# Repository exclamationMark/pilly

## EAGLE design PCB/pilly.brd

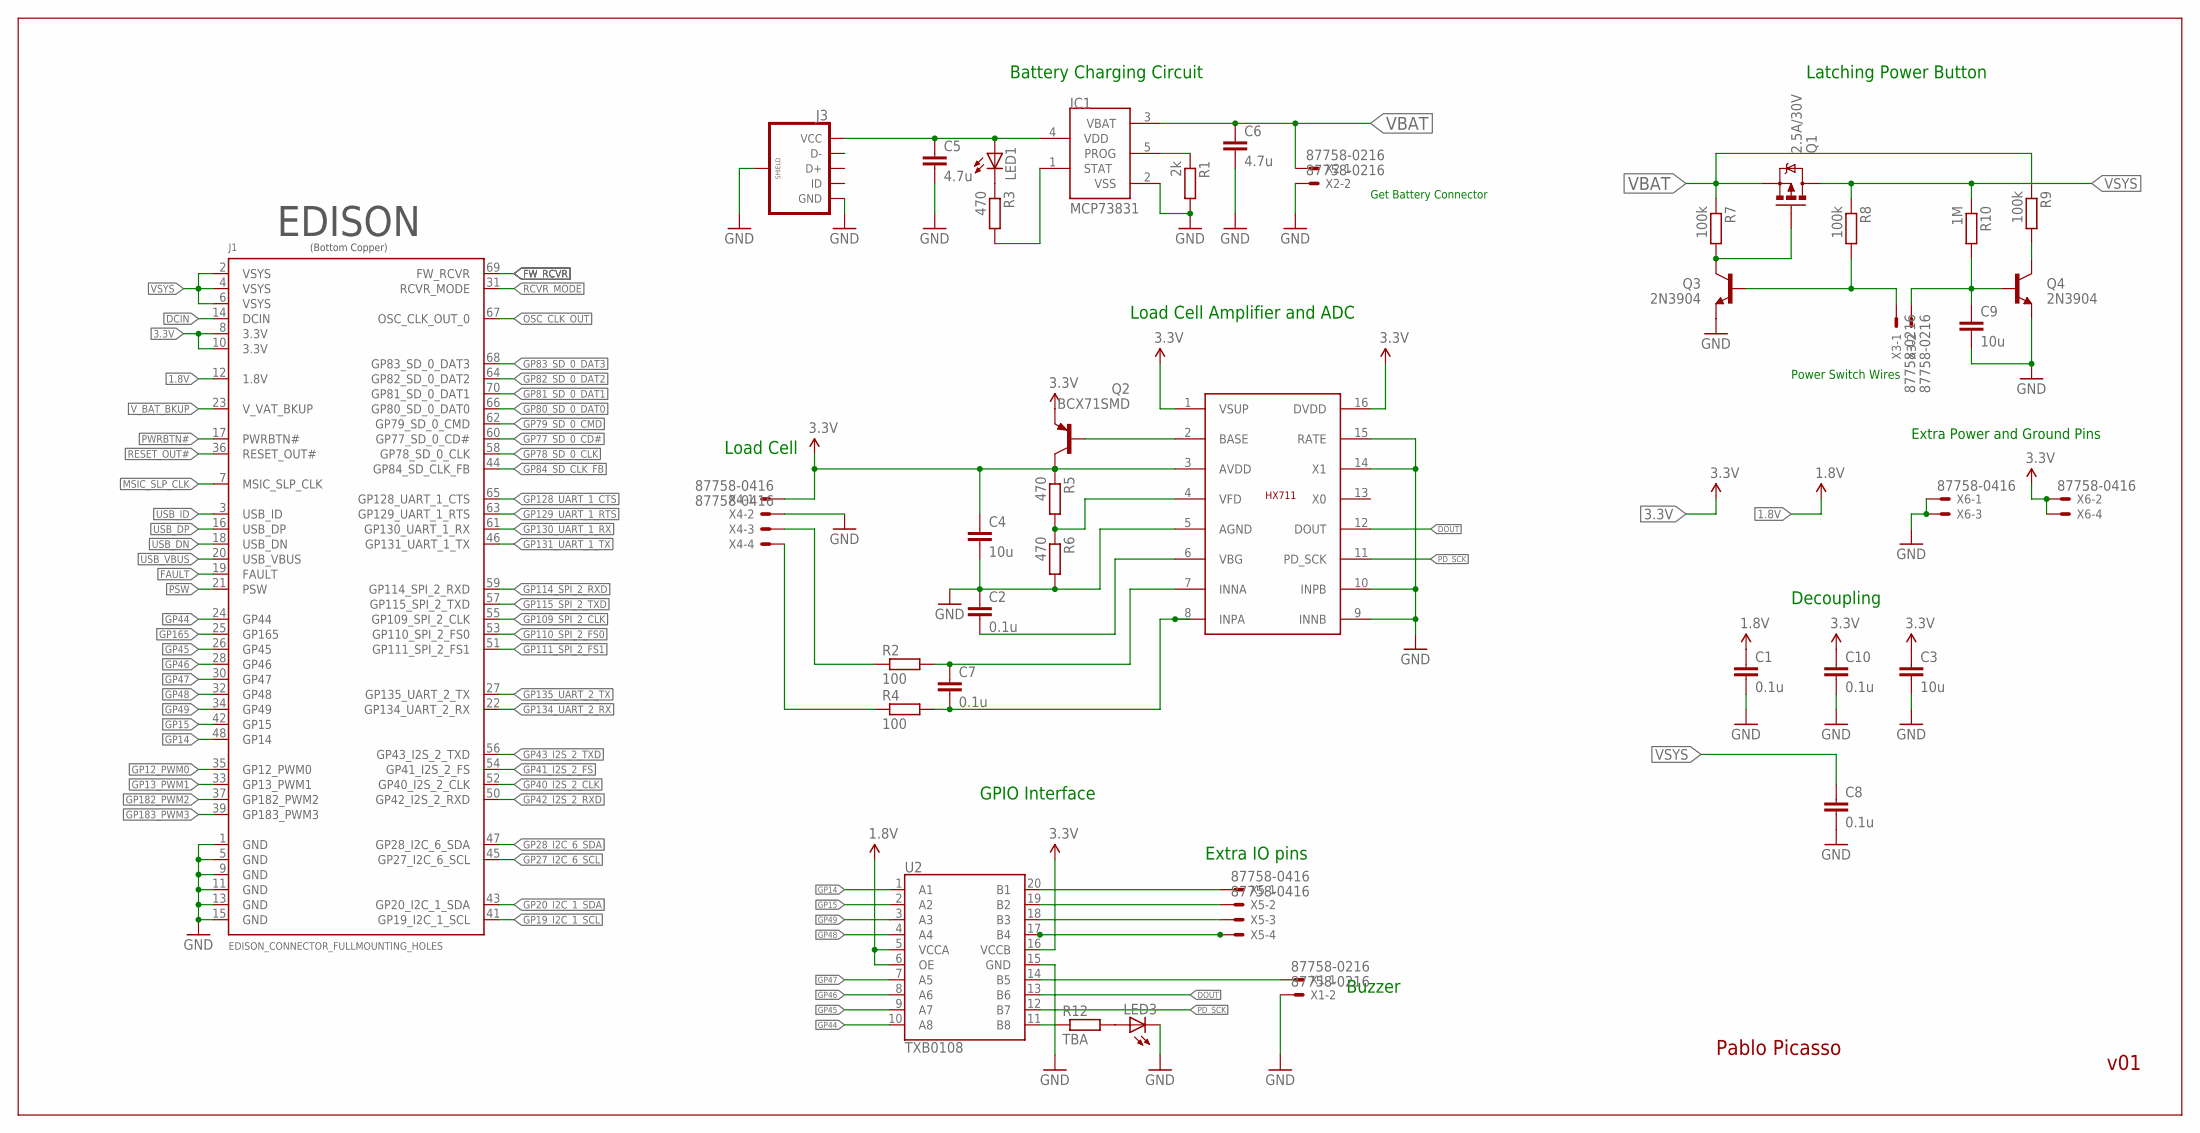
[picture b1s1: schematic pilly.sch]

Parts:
C1, C2, C7, C8, C10: 0.1u; C0805K
C3, C4, C9: 10u; C0805K
C5, C6: 4.7u; C0805K
IC1: MCP73831; SOT23-5L
J1: EDISON_CONNECTOR_FULLMOUNTING_HOLES; EDISON_DAUGHTER
J3: USB_MICROB_PLUGCONN-11752; USB-B-MICRO-SMD_V03
LED1, LED3: LEDCHIPLED_0805; CHIPLED_0805
Q1: 2.5A/30V; SOT23-3
Q2: BCX71SMD; SOT23
Q3, Q4: 2N3904; SOT23-3
R1: 2k; R0603
R2, R4: 100; R0603
R3, R5, R6: 470; R0603
R7, R8, R9: 100k; R0603
R10: 1M; R0603
R12: TBA; R0603
U2: TXB0108; UFDFN-20
U$1: HX711; SO16
X1, X2, X3: 87758-0216
X4, X5, X6: 87758-0416

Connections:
1.8V: C1.1, J1.12 (1.8V), U2.5 (VCCA), U2.6 (OE)
3.3V: C3.1, C4.1, C10.1, J1.8 (3.3V), J1.10 (3.3V), Q2.2 (E), Q2.3 (C), R5.1, U2.16 (VCCB), U$1.1 (VSUP), U$1.3 (AVDD), U$1.16 (DVDD), X4.1, X6.2, X6.4
DCIN: J1.14 (DCIN)
DOUT: U2.13 (B6), U$1.12 (DOUT)
FAULT: J1.19 (FAULT)
FW_RCVR: J1.69 (FW_RCVR)
GND: C1.2, C2.1, C3.2, C4.2, C5.2, C6.2, C8.2, C9.2, C10.2, IC1.2 (VSS), J1.1 (GND), J1.5 (GND), J1.9 (GND), J1.11 (GND), J1.13 (GND), J1.15 (GND), J3.GND, J3.SHIELD1 (SHIELD), J3.SHIELD2 (SHIELD), J3.SHIELD3 (SHIELD), LED3.C, Q3.2 (E), Q4.2 (E), R1.2, R6.2, U2.15 (GND), U$1.5 (AGND), U$1.9 (INNB), U$1.10 (INPB), U$1.14 (X1), U$1.15 (RATE), X1.2, X2.2, X4.2, X6.1, X6.3
GP12_PWM0: J1.35 (GP12_PWM0)
GP13_PWM1: J1.33 (GP13_PWM1)
GP14: J1.48 (GP14), U2.1 (A1)
GP15: J1.42 (GP15), U2.2 (A2)
GP19_I2C_1_SCL: J1.41 (GP19_I2C_1_SCL)
GP20_I2C_1_SDA: J1.43 (GP20_I2C_1_SDA)
GP27_I2C_6_SCL: J1.45 (GP27_I2C_6_SCL)
GP28_I2C_6_SDA: J1.47 (GP28_I2C_6_SDA)
GP40_I2S_2_CLK: J1.52 (GP40_I2S_2_CLK)
GP41_I2S_2_FS: J1.54 (GP41_I2S_2_FS)
GP42_I2S_2_RXD: J1.50 (GP42_I2S_2_RXD)
GP43_I2S_2_TXD: J1.56 (GP43_I2S_2_TXD)
GP44: J1.24 (GP44), U2.10 (A8)
GP45: J1.26 (GP45), U2.9 (A7)
GP46: J1.28 (GP46), U2.8 (A6)
GP47: J1.30 (GP47), U2.7 (A5)
GP48: J1.32 (GP48), U2.4 (A4)
GP49: J1.34 (GP49), U2.3 (A3)
GP77_SD_0_CD#: J1.60 (GP77_SD_0_CD#)
GP78_SD_0_CLK: J1.58 (GP78_SD_0_CLK)
GP79_SD_0_CMD: J1.62 (GP79_SD_0_CMD)
GP80_SD_0_DAT0: J1.66 (GP80_SD_0_DAT0)
GP81_SD_0_DAT1: J1.70 (GP81_SD_0_DAT1)
GP82_SD_0_DAT2: J1.64 (GP82_SD_0_DAT2)
GP83_SD_0_DAT3: J1.68 (GP83_SD_0_DAT3)
GP84_SD_CLK_FB: J1.44 (GP84_SD_CLK_FB)
GP109_SPI_2_CLK: J1.55 (GP109_SPI_2_CLK)
GP110_SPI_2_FS0: J1.53 (GP110_SPI_2_FS0)
GP111_SPI_2_FS1: J1.51 (GP111_SPI_2_FS1)
GP114_SPI_2_RXD: J1.59 (GP114_SPI_2_RXD)
GP115_SPI_2_TXD: J1.57 (GP115_SPI_2_TXD)
GP128_UART_1_CTS: J1.65 (GP128_UART_1_CTS)
GP129_UART_1_RTS: J1.63 (GP129_UART_1_RTS)
GP130_UART_1_RX: J1.61 (GP130_UART_1_RX)
GP131_UART_1_TX: J1.46 (GP131_UART_1_TX)
GP134_UART_2_RX: J1.22 (GP134_UART_2_RX)
GP135_UART_2_TX: J1.27 (GP135_UART_2_TX)
GP165: J1.25 (GP165)
GP182_PWM2: J1.37 (GP182_PWM2)
GP183_PWM3: J1.39 (GP183_PWM3)
MSIC_SLP_CLK: J1.7 (MSIC_SLP_CLK)
unnamed: LED1.C, R3.1
unnamed: IC1.5 (PROG), R1.1
unnamed: U2.14 (B5), X1.1
unnamed: R5.2, R6.1, U$1.4 (VFD)
unnamed: IC1.1 (STAT), R3.2
unnamed: C7.1, R2.2, U$1.7 (INNA)
unnamed: C7.2, R4.2, U$1.8 (INPA)
unnamed: C2.2, U$1.6 (VBG)
unnamed: Q2.1 (B), U$1.2 (BASE)
unnamed: R2.1, X4.3
unnamed: R4.1, X4.4
unnamed: U2.20 (B1), X5.1
unnamed: Q1.1 (G), Q3.3 (C), R7.2
unnamed: Q4.3 (C), R9.2
unnamed: C9.1, Q4.1 (B), R10.2, X3.2
unnamed: U2.19 (B2), X5.2
unnamed: U2.18 (B3), X5.3
unnamed: Q3.1 (B), R8.2, X3.1
unnamed: LED3.A, R12.2
unnamed: U2.17 (B4), X5.4
unnamed: R12.1, U2.11 (B8)
OSC_CLK_OUT: J1.67 (OSC_CLK_OUT_0)
PD_SCK: U2.12 (B7), U$1.11 (PD_SCK)
PSW: J1.21 (PSW)
PWRBTN#: J1.17 (PWRBTN#)
RCVR_MODE: J1.31 (RCVR_MODE)
RESET_OUT#: J1.36 (RESET_OUT#)
USB_DN: J1.18 (USB_DN)
USB_DP: J1.16 (USB_DP)
USB_ID: J1.3 (USB_ID)
USB_VBUS: J1.20 (USB_VBUS)
VBAT: C6.1, IC1.3 (VBAT), Q1.2 (S), R7.1, R9.1, X2.1
VIN: C5.1, IC1.4 (VDD), J3.VBUS (VCC), LED1.A
VSYS: C8.1, J1.2 (VSYS), J1.4 (VSYS), J1.6 (VSYS), Q1.3 (D), R8.1, R10.1
V_BAT_BKUP: J1.23 (V_VAT_BKUP)

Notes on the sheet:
v01
Battery Charging Circuit
Load Cell Amplifier and ADC
Extra IO pins
Latching Power Button
Power Switch Wires
Load Cell
Buzzer
Get Battery Connector
Decoupling
GPIO Interface
EDISON
(Bottom Copper)
Pablo Picasso
Extra Power and Ground Pins

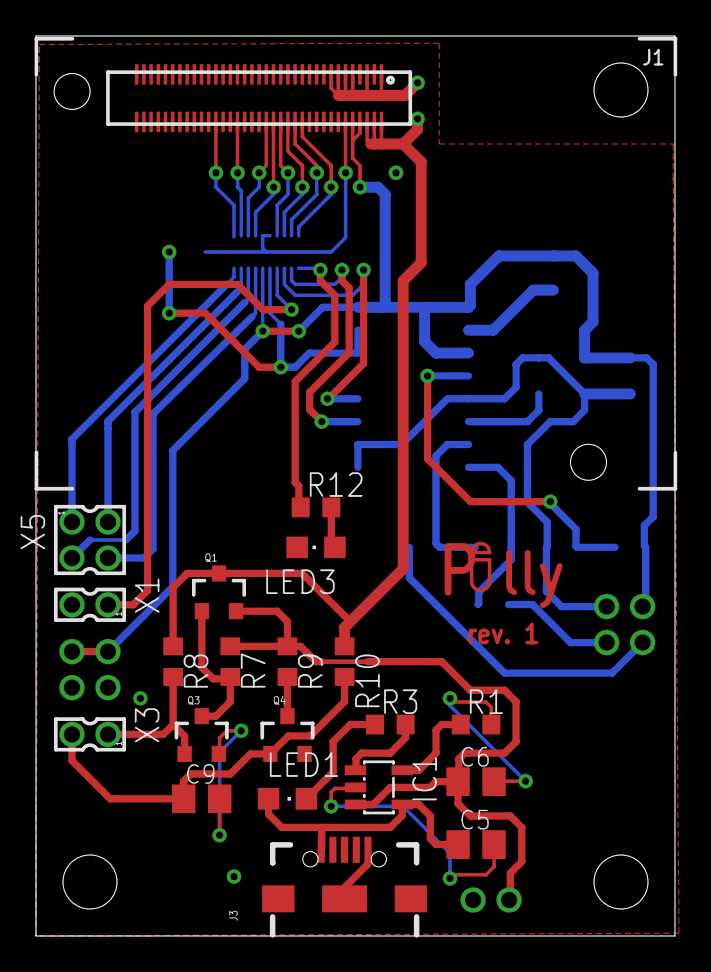
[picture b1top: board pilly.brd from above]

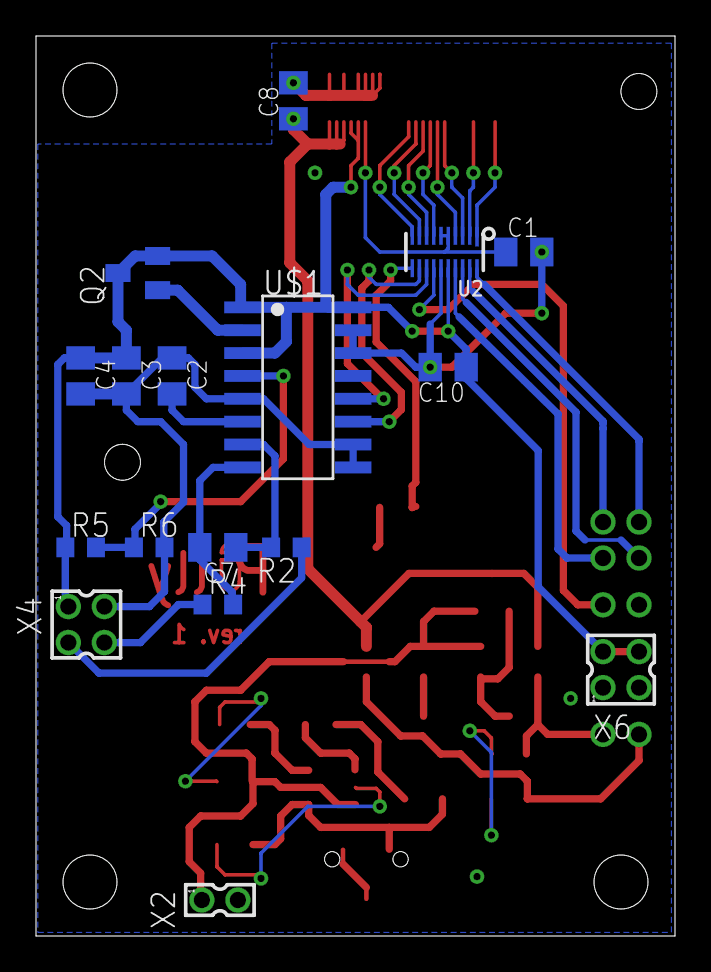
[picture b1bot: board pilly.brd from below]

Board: 2 copper layers, 35.5 x 50.0 mm, 38 parts (17 on the bottom side), 37 nets.

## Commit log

2016-03-23 initial comit, woo!
2016-03-23 web stuff
2016-03-23 Removed control_panel backup
2016-03-23 Merged style.css and control.css into one file (style.css). Started styling login page. Added test.py for local testing.
2016-03-23 MOAR login styling
2016-03-23 Root of websites now renders 'index.html' template. Added login app route.
2016-03-23 Oops... added leading slash
2016-03-23 Finished styling login page
2016-03-23 serverconfig.json file for configuring the server from a file
2016-03-23 Converted top navbar to scroll-in menu. Added script to scroll in said menu.
2016-03-23 Added background dimming when opening the menu
2016-03-23 Can now close the menu by clicking out of it.
2016-03-30 Changed login button styling
2016-03-30 Converted the table to divs, so it animates nicely. Added javascript function to insert a new table row (newElement(timestamp, eventname) ), try it out by clicking on the pill number.
2016-03-30 Removed unnecessary stuff
2016-04-20 Added 'remember me' checkbox in the login page. Check 'test.py' for usage
2016-04-24 Working code for reading HX711
    The code with the correct delay for reading from the HX711. Gives
    seemingly reasonable values.
2016-04-29 Added (not working) c file
2016-04-29 Now it's kinda working
2016-05-01 Making the read work using C
    The clk signal looks good and we fixed problems with the scheduler
    messing up the timing etc but we are not able to read the value for
    some reason
2016-05-01 Somewhat reliable weight_read
    reads 11 valid (not all ones) values and takes the median.
2016-05-01 Added Android app
2016-05-01 new version of the server script. Now with class!
2016-05-03 The app now fetches info from the server, thanks to JessicaFetcher
2016-05-03 All info is now shown on the status Activity
2016-06-01 Board
    Added the schematic and the board for Pilly
2016-06-02 Small changes to the board
    Added a fourth hole in case we want to use it.
2016-07-22 Fetching user data now doesn't block the UI thread. Also, I remade everything from scratch.
2016-07-22 Added loading wheel when fetching data
2016-07-22 Removed unnecessary comments
2016-07-23 Began implementing the Schedule activity
2016-07-23 Added menu icons
2016-07-23 Added long press to select on schedule
2016-07-23 Added long-press context menu
2016-07-23 Added activity to configure a new alert
2016-07-24 Added time picker to new alert activity
2016-07-24 Changed Schedule activity so it implements the listeners
2016-07-25 Converted PillAlert to Parcelable, so it can be passed through an intent. NewAlert is now started through startActivitForResult. Converted days from enum array to int array
2016-07-25 Can now edit the alert time
2016-07-25 Fixed string resources
2016-07-25 Added days selection. Contextual menu now closes after click
2016-07-25 Added pill quantity selector
2016-07-25 Fixed time display issue in schedule
2016-07-26 Increased minimum SDK to include number picker. Corrected color scheme. Alerts get now sorted by time automatically. Added status menu options.
2016-07-26 Started building the alarm system
2016-07-29 Added AlarmHandler service to be fired on the next scheduled pillAlert
2016-07-29 List of scheduled pill alerts is now saved to and retrieved from a shared preference file
2016-07-29 Shifted days numbers in compliance with Calendar.DAY_OF_WEEK. Added PillAlert.getNextTrigger. Added Schedule.getEarliestAlert
2016-07-29 Added BroadcastReceiver to reset the alarm upon reboot. Started implementing alarm system
2016-07-30 Added script to retrieve next scheduled alarm. Add, edit and delete menu buttons now correctly schedule next alarm
2016-07-30 Added connectivity check to alarm handler
2016-07-30 Added alarm screen. I plays sounds and wakes up the device! Neat.
2016-07-30 Sound now stops on screen lock
2016-07-30 Implemented snooze feature
2016-07-30 Tidy up
2016-07-30 Added no alerts scheduled screen
2016-07-30 Unnecessarily corrected a typo
2016-08-01 Whatever
2016-08-24 Does anybody even read these?
2016-08-28 Next Pill Time is now calculated by the app
2016-08-28 Server changes
2016-08-29 Extended server capabilities
2016-08-29 Added server home page
2016-08-29 blah
2016-08-29 I don't have time for commit messages
2016-08-29 Recent events are human readable
2016-08-29 System is now ready to handle overdoses
2016-08-30 Added 'all events' screen
2016-08-30 dirty hack
2016-09-13 Started making armada's candy counter
2016-09-13 Armada page continued
2016-09-14 Finished Armada candy counter
2016-09-15 initialise history on initialising a new Pilly
2016-09-15 fixed history initialisation
2016-09-15 event IDs
2016-09-15 Enable event ID check
2016-09-15 Fixed IP
2016-09-15 lol int cast

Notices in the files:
parts and their libraries:
SparkFun-Connectors: Licensing: Creative Commons ShareAlike 4.0 International - https://creativecommons.org/licenses/by-sa/4.0
